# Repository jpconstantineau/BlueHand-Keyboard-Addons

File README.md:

# BlueHand-Keyboard-Addons
Design files for the BlueHand keyboard

For documentation on the BlueHand, see [here](http://nrf52.jpconstantineau.com/docs/macropad/bluehand)

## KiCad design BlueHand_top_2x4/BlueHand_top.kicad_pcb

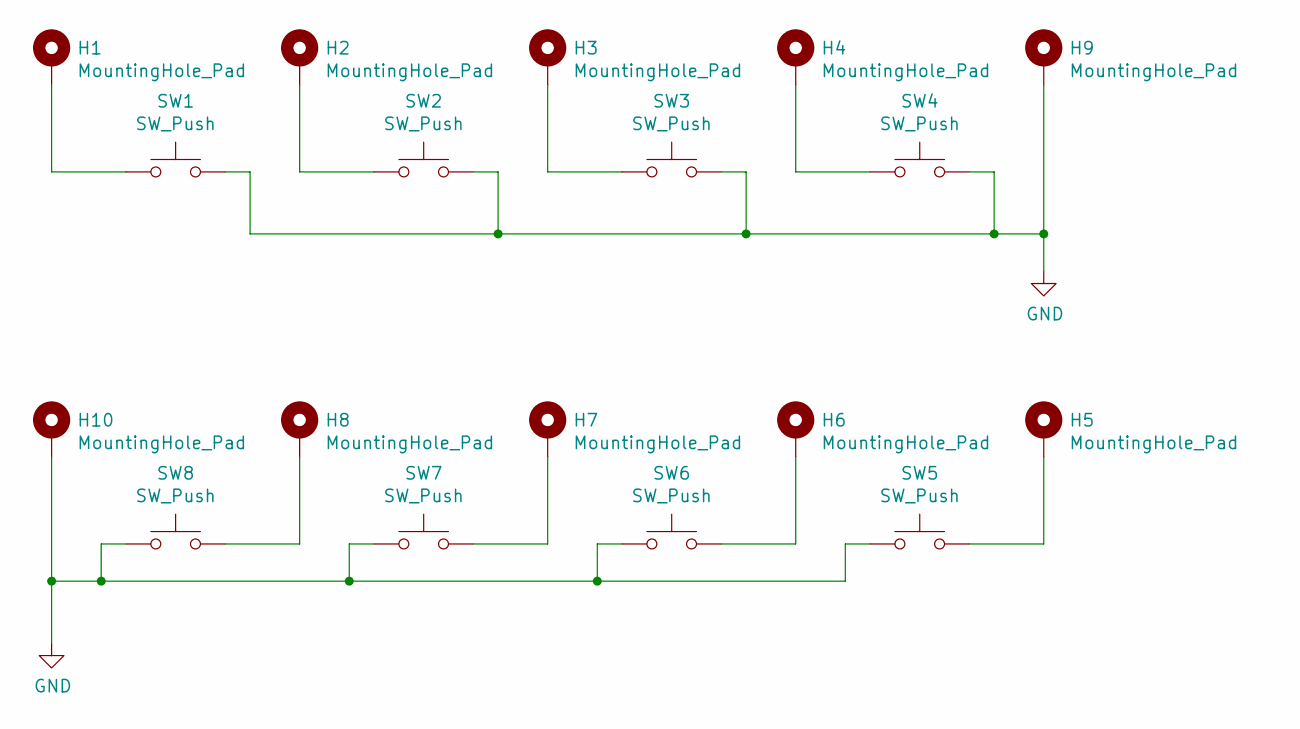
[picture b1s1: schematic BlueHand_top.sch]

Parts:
H1, H2, H3, H4, H5, H6, H7, H8, H9, H10: MountingHole_Pad; MountingHole_2.2mm_M2_Pad_TopBottom
SW1, SW2, SW3, SW4, SW5, SW6, SW7, SW8: SW_Push; MX-Alps-Choc-1U

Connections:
GND: H9.1, H10.1, SW1.2, SW2.2, SW3.2, SW4.2, SW5.1, SW6.1, SW7.1, SW8.1
unnamed: H1.1, SW1.1
unnamed: H2.1, SW2.1
unnamed: H3.1, SW3.1
unnamed: H4.1, SW4.1
unnamed: H5.1, SW5.2
unnamed: H6.1, SW6.2
unnamed: H7.1, SW7.2
unnamed: H8.1, SW8.2

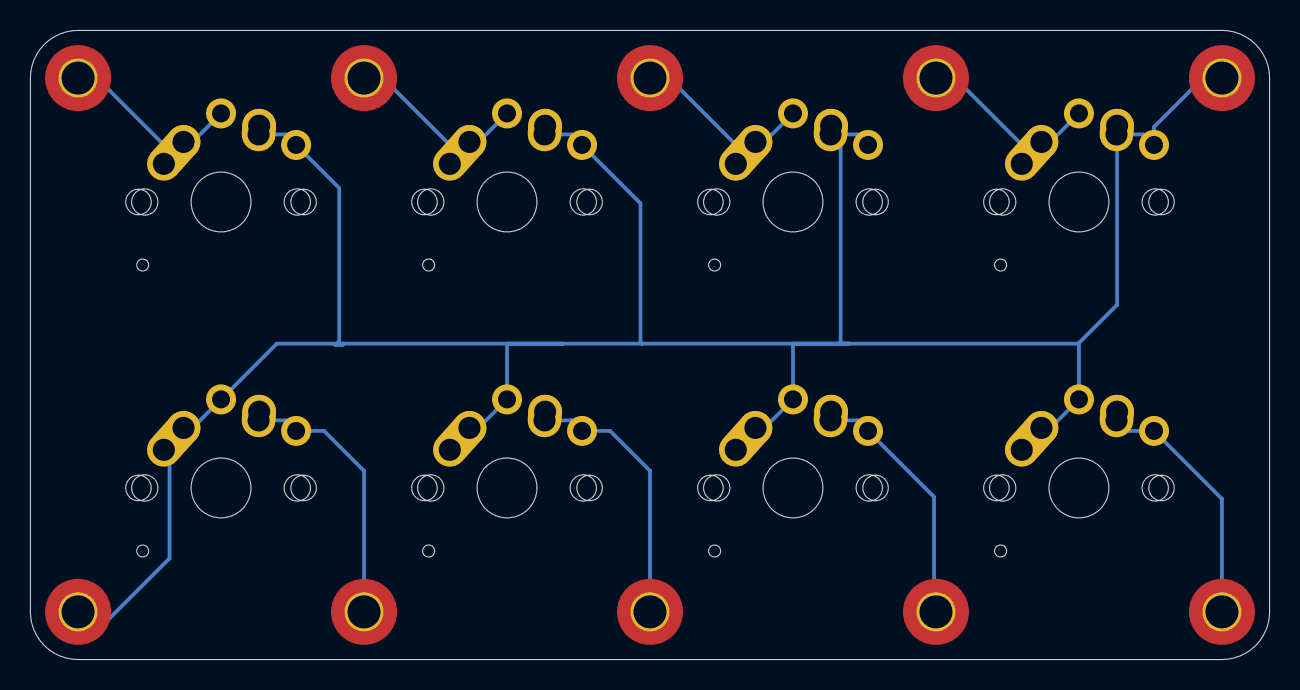
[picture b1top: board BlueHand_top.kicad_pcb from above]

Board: 2 copper layers, 82.6 x 41.9 mm, 18 parts (0 on the bottom side), 9 nets.

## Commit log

2021-05-21 added initial files
2021-08-08 updataed mid to v3
2022-08-14 added new mid plate - helps not confuse the laser cutter not mess things up and skip things
